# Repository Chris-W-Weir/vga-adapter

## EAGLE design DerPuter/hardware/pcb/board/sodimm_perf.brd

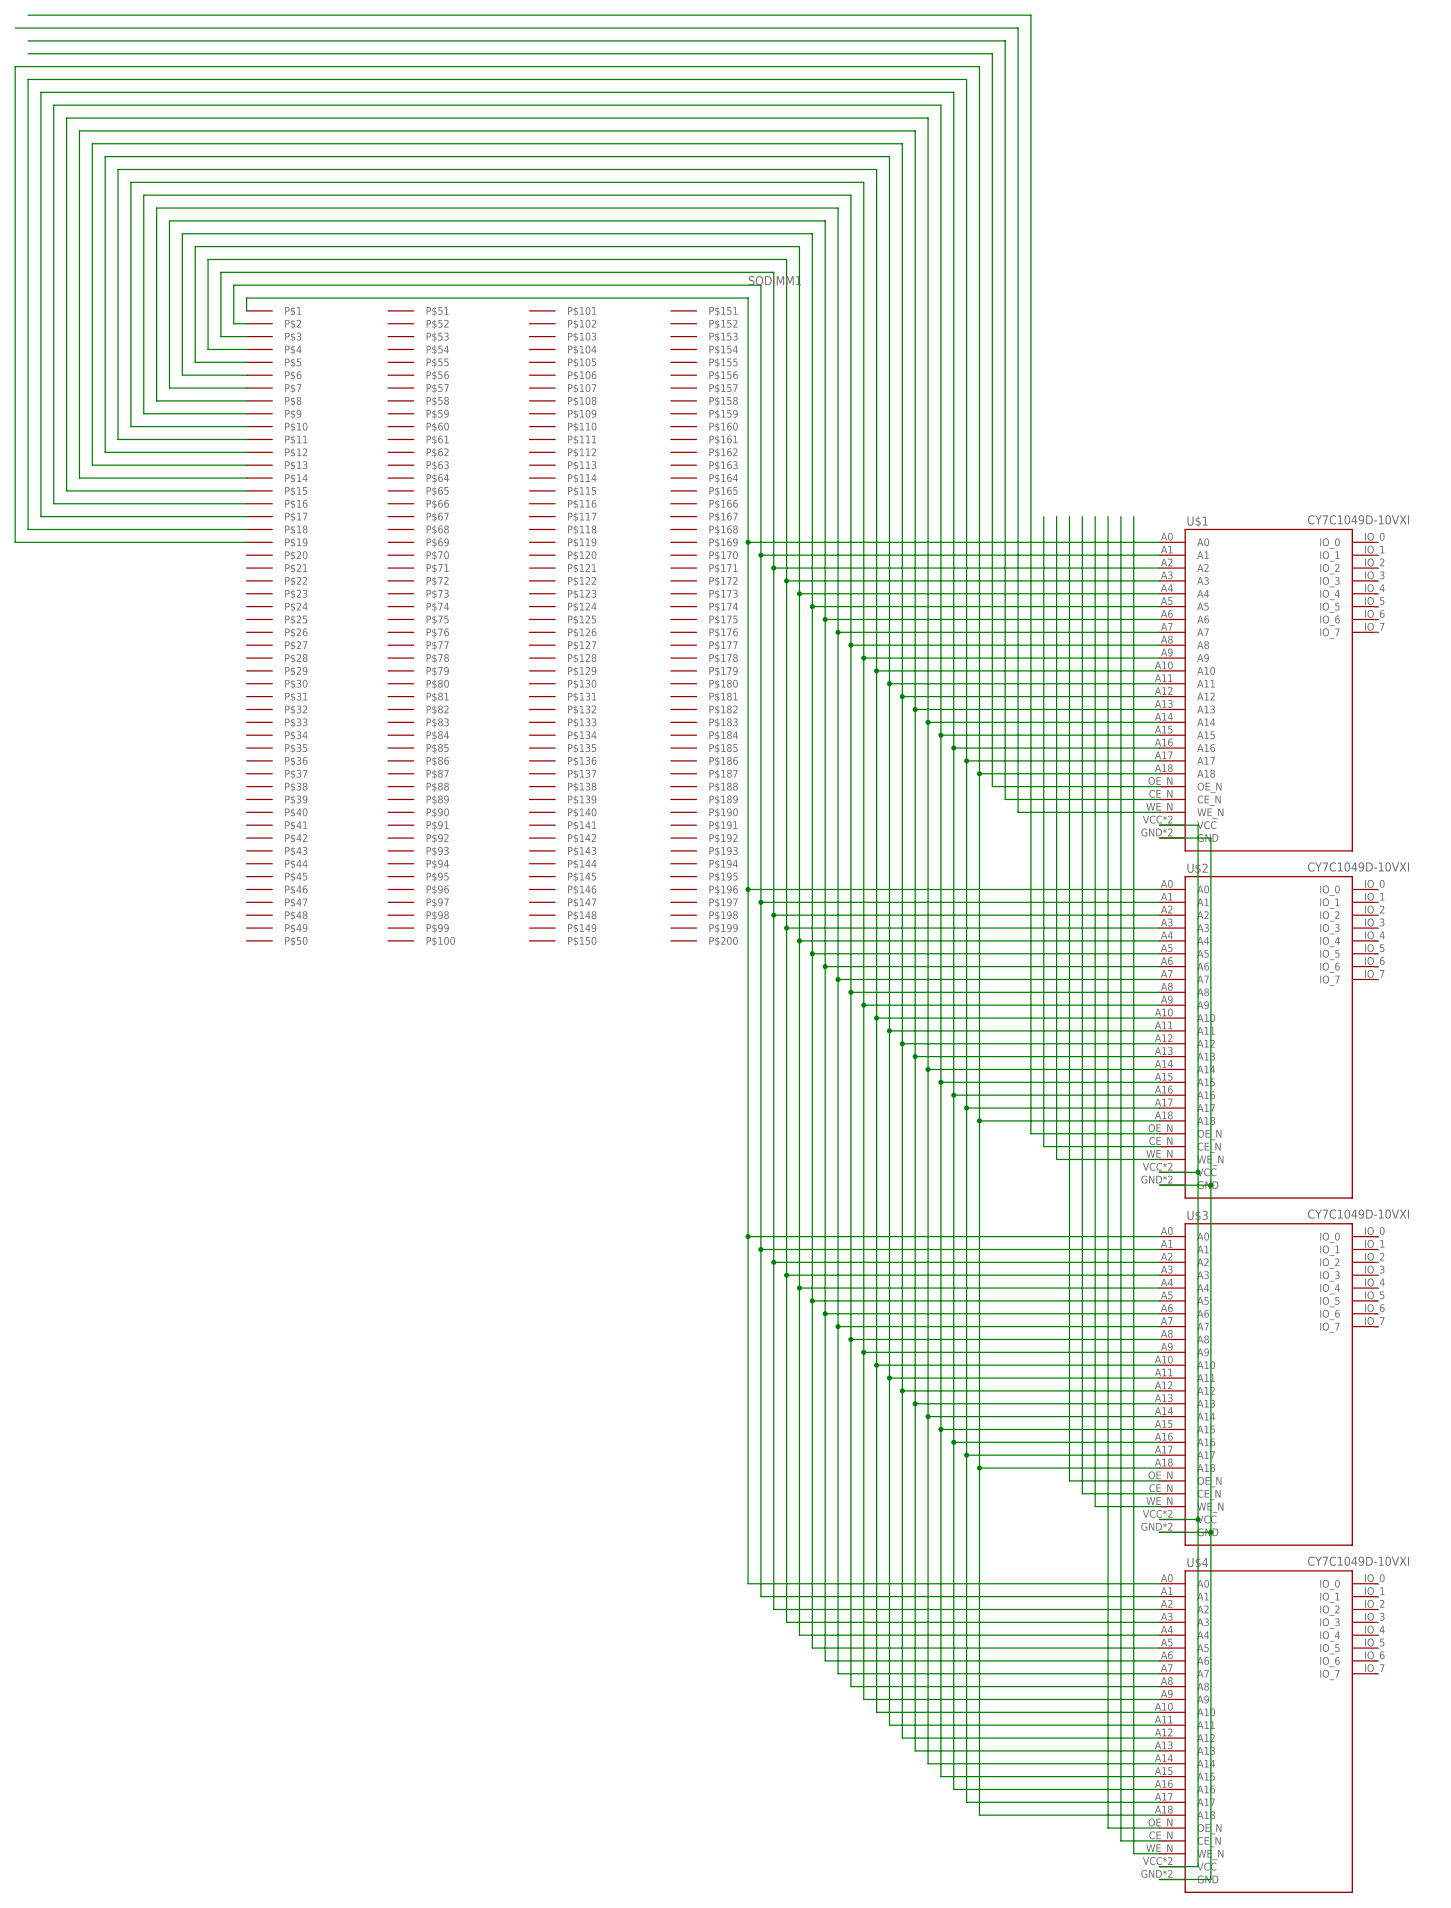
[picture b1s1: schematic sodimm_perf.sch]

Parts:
SODIMM1: SODIMM_BOARD; SODIMM_BOARD-67.6X42.5
U$1, U$2, U$3, U$4: CY7C1049D-10VXI; SOJ36

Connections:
unnamed: SODIMM1.1, U$1.A0, U$2.A0, U$3.A0, U$4.A0
unnamed: SODIMM1.2, U$1.A1, U$2.A1, U$3.A1, U$4.A1
unnamed: SODIMM1.3, U$1.A2, U$2.A2, U$3.A2, U$4.A2
unnamed: SODIMM1.4, U$1.A3, U$2.A3, U$3.A3, U$4.A3
unnamed: SODIMM1.5, U$1.A4, U$2.A4, U$3.A4, U$4.A4
unnamed: SODIMM1.6, U$1.A5, U$2.A5, U$3.A5, U$4.A5
unnamed: SODIMM1.7, U$1.A6, U$2.A6, U$3.A6, U$4.A6
unnamed: SODIMM1.10, U$1.A9, U$2.A9, U$3.A9, U$4.A9
unnamed: SODIMM1.11, U$1.A10, U$2.A10, U$3.A10, U$4.A10
unnamed: SODIMM1.12, U$1.A11, U$2.A11, U$3.A11, U$4.A11
unnamed: SODIMM1.13, U$1.A12, U$2.A12, U$3.A12, U$4.A12
unnamed: SODIMM1.14, U$1.A13, U$2.A13, U$3.A13, U$4.A13
unnamed: SODIMM1.15, U$1.A14, U$2.A14, U$3.A14, U$4.A14
unnamed: SODIMM1.16, U$1.A15, U$2.A15, U$3.A15, U$4.A15
unnamed: SODIMM1.8, U$1.A7, U$2.A7, U$3.A7, U$4.A7
unnamed: SODIMM1.9, U$1.A8, U$2.A8, U$3.A8, U$4.A8
unnamed: SODIMM1.17, U$1.A16, U$2.A16, U$3.A16, U$4.A16
unnamed: SODIMM1.18, U$1.A17, U$2.A17, U$3.A17, U$4.A17
unnamed: SODIMM1.19, U$1.A18, U$2.A18, U$3.A18, U$4.A18
unnamed: U$1.VCC, U$1.VCC_ (VCC), U$2.VCC, U$2.VCC_ (VCC), U$3.VCC, U$3.VCC_ (VCC), U$4.VCC, U$4.VCC_ (VCC)
unnamed: U$1.GND, U$1.GND_ (GND), U$2.GND, U$2.GND_ (GND), U$3.GND, U$3.GND_ (GND), U$4.GND, U$4.GND_ (GND)

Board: 2 copper layers, 5 parts (0 on the bottom side), 21 nets, no tracks yet.

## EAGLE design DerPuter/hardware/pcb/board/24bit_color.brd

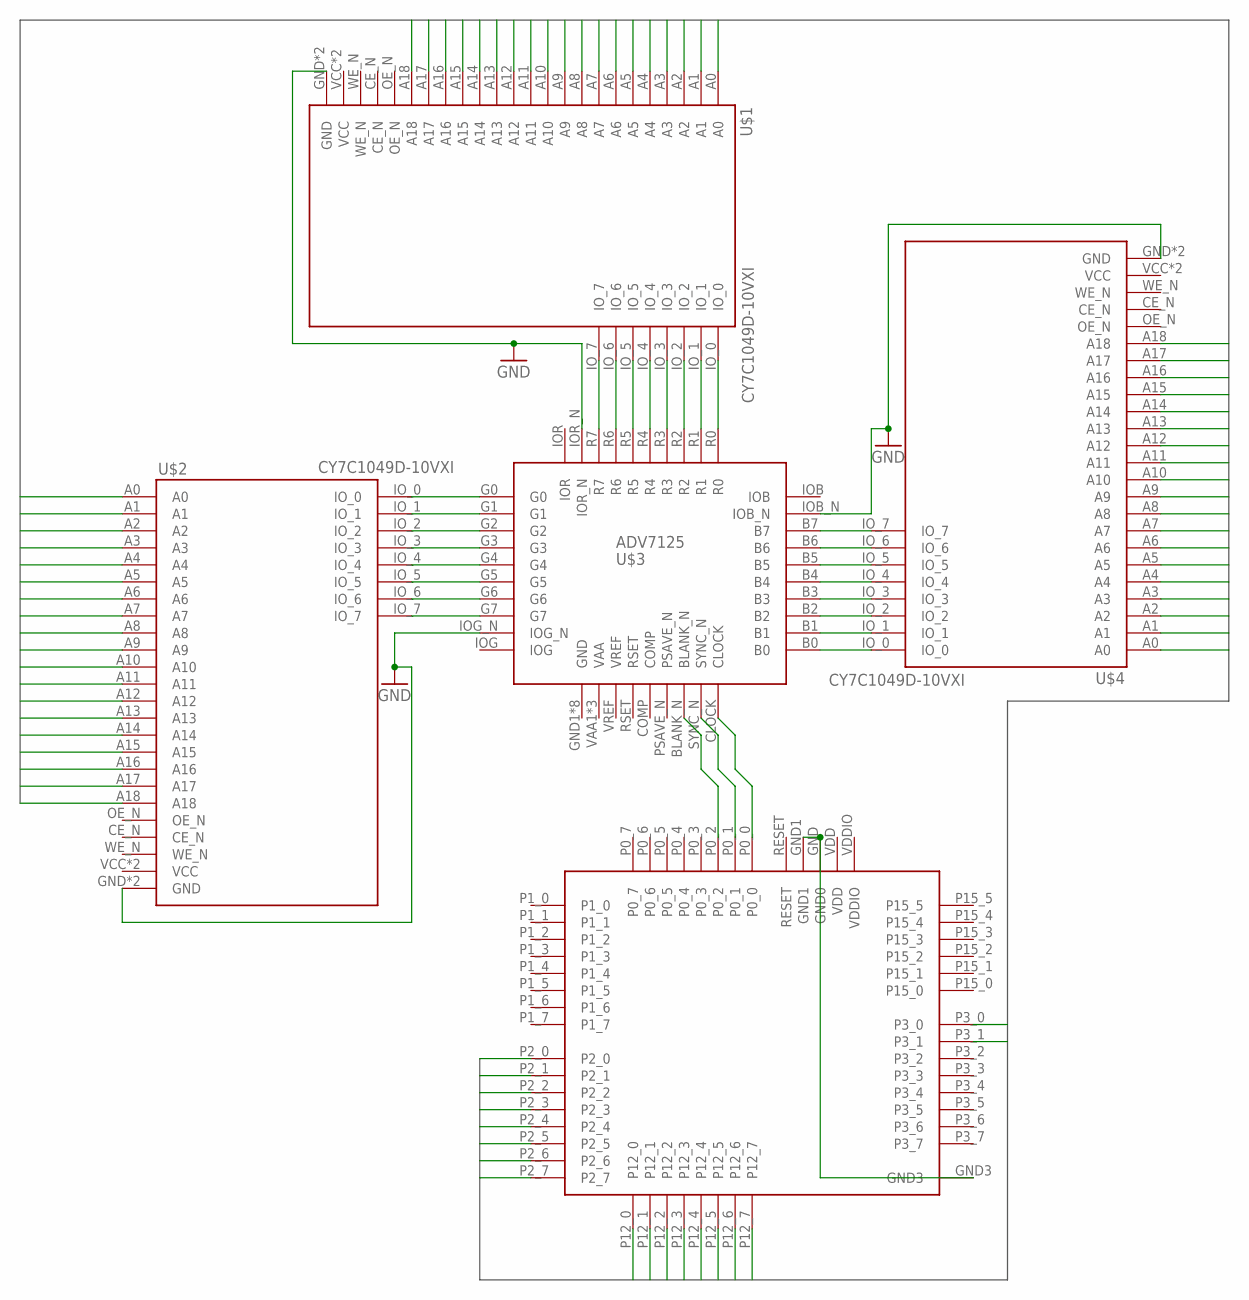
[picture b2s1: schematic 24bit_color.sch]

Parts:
U$1, U$2, U$4: CY7C1049D-10VXI; SOJ36
U$3: ADV7125; LQFP48
U$5: CY8CKIT-059; PSOC_STICK

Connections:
ADR0: U$1.A0, U$2.A0, U$4.A0, U$5.P2_0
ADR1: U$1.A1, U$2.A1, U$4.A1, U$5.P2_1
ADR2: U$1.A2, U$2.A2, U$4.A2, U$5.P2_2
ADR3: U$1.A3, U$2.A3, U$4.A3, U$5.P2_3
ADR4: U$1.A4, U$2.A4, U$4.A4, U$5.P2_4
ADR5: U$1.A5, U$2.A5, U$4.A5, U$5.P2_5
ADR6: U$1.A6, U$2.A6, U$4.A6, U$5.P2_6
ADR7: U$1.A7, U$2.A7, U$4.A7, U$5.P2_7
ADR8: U$1.A8, U$2.A8, U$4.A8, U$5.P12_0
ADR9: U$1.A9, U$2.A9, U$4.A9, U$5.P12_1
ADR10: U$1.A10, U$2.A10, U$4.A10, U$5.P12_2
ADR11: U$1.A11, U$2.A11, U$4.A11, U$5.P12_3
ADR12: U$1.A12, U$2.A12, U$4.A12, U$5.P12_4
ADR13: U$1.A13, U$2.A13, U$4.A13, U$5.P12_5
ADR14: U$1.A14, U$2.A14, U$4.A14, U$5.P12_6
ADR15: U$1.A15, U$2.A15, U$4.A15, U$5.P12_7
ADR16: U$1.A16, U$2.A16, U$4.A16, U$5.P3_0
ADR17: U$1.A17, U$2.A17, U$4.A17, U$5.P3_1
ADR18: U$1.A18, U$2.A18, U$4.A18
GND: U$1.GND, U$1.GND_ (GND), U$2.GND, U$2.GND_ (GND), U$3.GND1 (GND), U$3.GND2 (GND), U$3.GND3 (GND), U$3.GND4 (GND), U$3.GND5 (GND), U$3.GND6 (GND), U$3.GND7 (GND), U$3.GND8 (GND), U$3.IOB_N, U$3.IOG_N, U$3.IOR_N, U$4.GND, U$4.GND_ (GND)
unnamed: U$2.IO_0, U$3.G0
unnamed: U$2.IO_1, U$3.G1
unnamed: U$2.IO_2, U$3.G2
unnamed: U$2.IO_3, U$3.G3
unnamed: U$2.IO_4, U$3.G4
unnamed: U$2.IO_5, U$3.G5
unnamed: U$2.IO_6, U$3.G6
unnamed: U$2.IO_7, U$3.G7
unnamed: U$1.IO_0, U$3.R0
unnamed: U$1.IO_1, U$3.R1
unnamed: U$1.IO_2, U$3.R2
unnamed: U$1.IO_3, U$3.R3
unnamed: U$1.IO_4, U$3.R4
unnamed: U$1.IO_5, U$3.R5
unnamed: U$1.IO_6, U$3.R6
unnamed: U$1.IO_7, U$3.R7
unnamed: U$3.B7, U$4.IO_7
unnamed: U$3.B6, U$4.IO_6
unnamed: U$3.B5, U$4.IO_5
unnamed: U$3.B4, U$4.IO_4
unnamed: U$3.B3, U$4.IO_3
unnamed: U$3.B2, U$4.IO_2
unnamed: U$3.B1, U$4.IO_1
unnamed: U$3.B0, U$4.IO_0
unnamed: U$3.CLOCK, U$5.P0_0
unnamed: U$5.GND (GND0), U$5.GND1, U$5.GND3
unnamed: U$3.SYNC_N, U$5.P0_1
unnamed: U$3.BLANK_N, U$5.P0_2
VAA: U$3.VAA1 (VAA), U$3.VAA2 (VAA), U$3.VAA3 (VAA)
VCC: U$1.VCC, U$1.VCC_ (VCC), U$2.VCC, U$2.VCC_ (VCC), U$4.VCC, U$4.VCC_ (VCC)
VDD: U$5.VDD
VDDIO: U$5.VDDIO

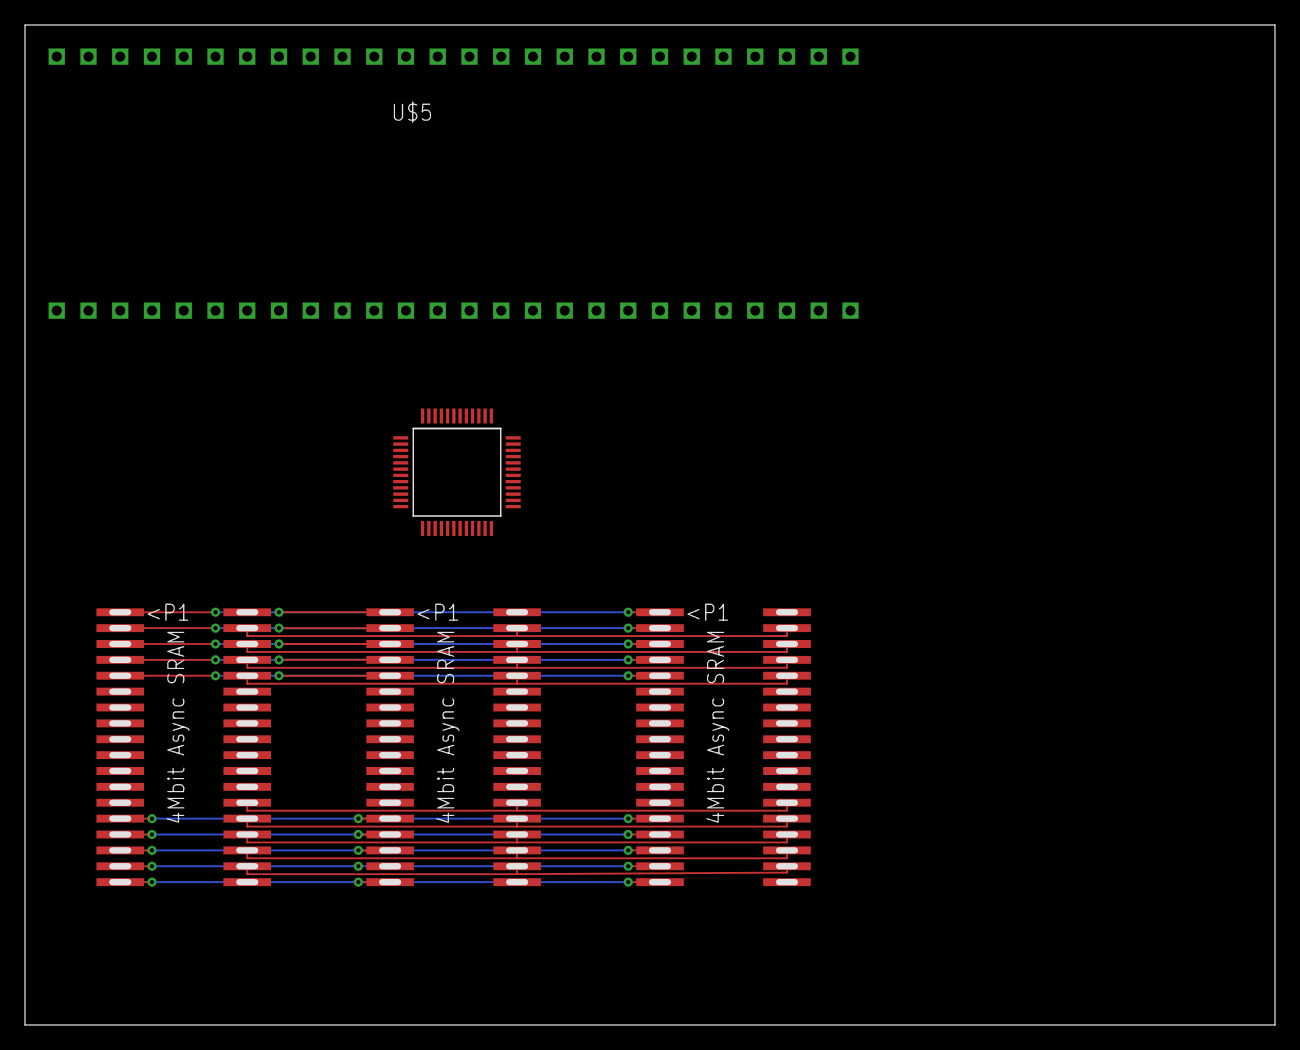
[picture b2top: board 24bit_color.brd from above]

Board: 2 copper layers, 100.0 x 80.0 mm, 5 parts (0 on the bottom side), 50 nets.

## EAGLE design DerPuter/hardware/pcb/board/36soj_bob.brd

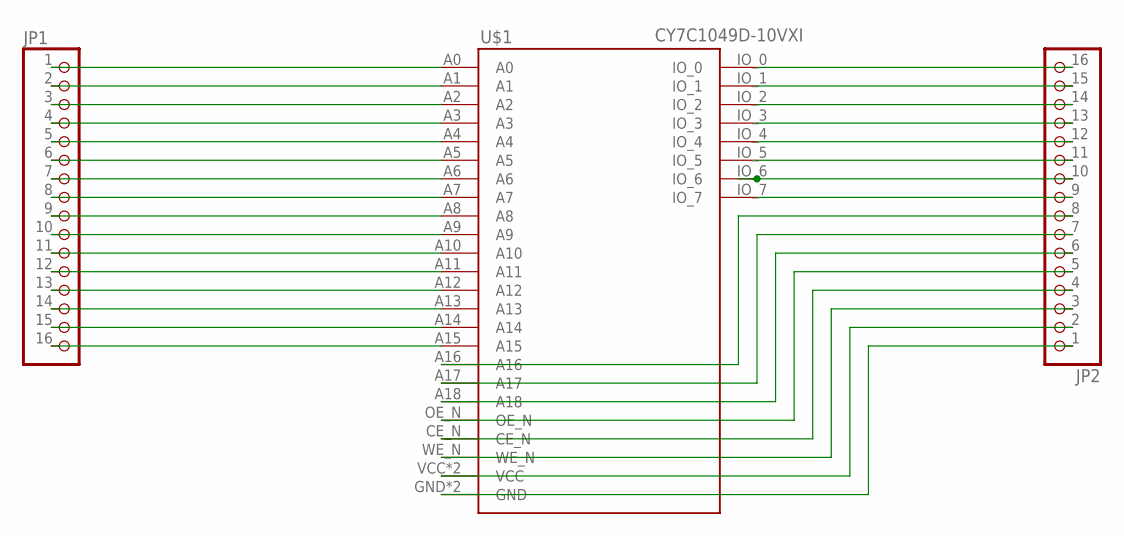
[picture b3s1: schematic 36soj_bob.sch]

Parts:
JP1, JP2: PINHD-1X16; 1X16
U$1: CY7C1049D-10VXI; SOJ36

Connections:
unnamed: JP2.16, U$1.IO_0
unnamed: JP2.15, U$1.IO_1
unnamed: JP2.14, U$1.IO_2
unnamed: JP2.13, U$1.IO_3
unnamed: JP2.12, U$1.IO_4
unnamed: JP2.11, U$1.IO_5
unnamed: JP2.10, U$1.IO_6
unnamed: JP2.9, U$1.IO_7
unnamed: JP1.1, U$1.A0
unnamed: JP1.2, U$1.A1
unnamed: JP1.3, U$1.A2
unnamed: JP1.4, U$1.A3
unnamed: JP1.5, U$1.A4
unnamed: JP1.6, U$1.A5
unnamed: JP1.7, U$1.A6
unnamed: JP1.8, U$1.A7
unnamed: JP1.9, U$1.A8
unnamed: JP1.10, U$1.A9
unnamed: JP1.11, U$1.A10
unnamed: JP1.12, U$1.A11
unnamed: JP1.13, U$1.A12
unnamed: JP1.14, U$1.A13
unnamed: JP1.15, U$1.A14
unnamed: JP1.16, U$1.A15
unnamed: JP2.8, U$1.A16
unnamed: JP2.7, U$1.A17
unnamed: JP2.6, U$1.A18
unnamed: JP2.5, U$1.OE_N
unnamed: JP2.4, U$1.CE_N
unnamed: JP2.3, U$1.WE_N
unnamed: JP2.2, U$1.VCC, U$1.VCC_ (VCC)
unnamed: JP2.1, U$1.GND, U$1.GND_ (GND)

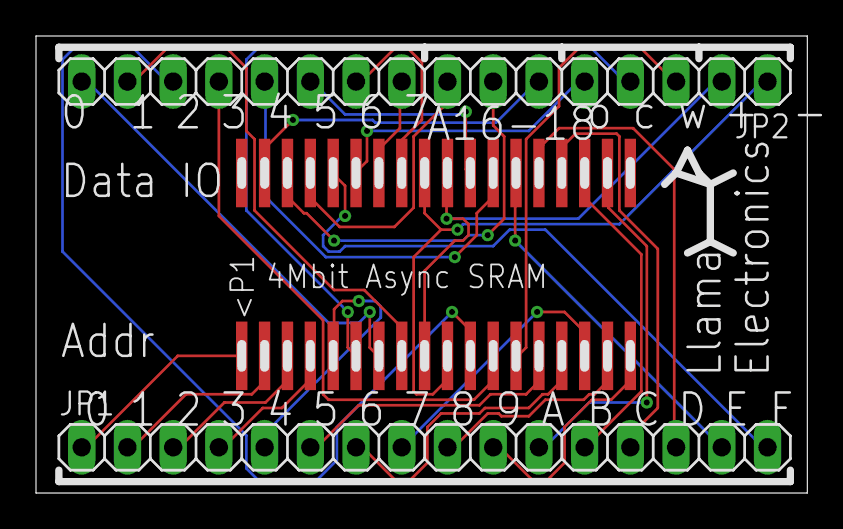
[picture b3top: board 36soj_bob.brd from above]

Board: 2 copper layers, 42.8 x 25.4 mm, 3 parts (0 on the bottom side), 32 nets.

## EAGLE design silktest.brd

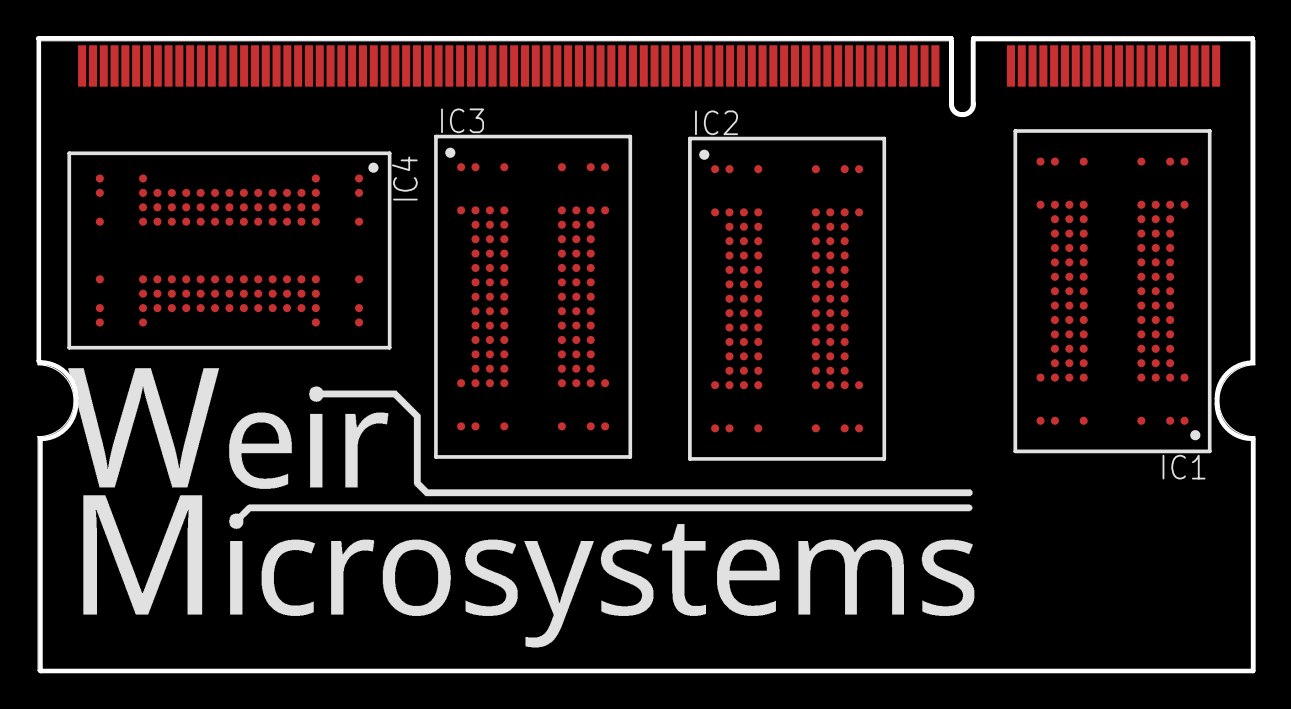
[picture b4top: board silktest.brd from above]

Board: 2 copper layers, 67.5 x 35.1 mm, 5 parts (0 on the bottom side), 86 nets, no tracks yet.

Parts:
IC1, IC2, IC3, IC4: K4B1G04(08/16)46C-128MB; FBGA-94-C
SODIMM1: SODIMM_BOARD_SMALLER-67.6X35

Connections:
unnamed: IC1.K4, SODIMM1.10
unnamed: IC1.J4, SODIMM1.9
unnamed: IC1.N4, SODIMM1.12
unnamed: IC1.P8, SODIMM1.13
unnamed: IC1.P4, SODIMM1.14
unnamed: IC1.N3, SODIMM1.15
unnamed: IC1.P9, SODIMM1.16
unnamed: IC1.P3, SODIMM1.17
unnamed: IC1.R9, SODIMM1.18
unnamed: IC1.R3, SODIMM1.19
unnamed: IC1.T9, SODIMM1.20
unnamed: IC1.R4, SODIMM1.21
unnamed: IC1.L8, SODIMM1.22
unnamed: IC1.R8, SODIMM1.23
unnamed: IC1.N8, SODIMM1.24
unnamed: IC1.H2, SODIMM1.1
unnamed: IC1.L9, SODIMM1.4
unnamed: IC1.M9, SODIMM1.2
unnamed: IC1.T3, SODIMM1.3
unnamed: IC1.L3, SODIMM1.11
unnamed: IC1.E8, SODIMM1.25
unnamed: IC2.K4, SODIMM1.36
unnamed: IC2.J4, SODIMM1.35
unnamed: IC2.N4, SODIMM1.38
unnamed: IC2.P8, SODIMM1.39
unnamed: IC2.P4, SODIMM1.40
unnamed: IC2.N3, SODIMM1.41
unnamed: IC2.P9, SODIMM1.42
unnamed: IC2.P3, SODIMM1.43
unnamed: IC2.R9, SODIMM1.44
unnamed: IC2.R3, SODIMM1.45
unnamed: IC2.T9, SODIMM1.46
unnamed: IC2.R4, SODIMM1.47
unnamed: IC2.L8, SODIMM1.48
unnamed: IC2.R8, SODIMM1.49
unnamed: IC2.N8, SODIMM1.50
unnamed: IC2.H2, SODIMM1.27
unnamed: IC2.L9, SODIMM1.30
unnamed: IC2.M9, SODIMM1.28
unnamed: IC1.L4, SODIMM1.26
unnamed: IC1.G4, SODIMM1.51
unnamed: IC1.F4, SODIMM1.52
unnamed: IC1.M3, SODIMM1.53
unnamed: IC1.N9, SODIMM1.54
unnamed: IC1.M4, SODIMM1.55
unnamed: IC1.E4, SODIMM1.56
unnamed: IC1.F8, SODIMM1.57
unnamed: IC1.F3, SODIMM1.58
unnamed: IC1.F9, SODIMM1.59
unnamed: IC2.T3, SODIMM1.60
unnamed: IC3.K4, SODIMM1.186
unnamed: IC3.J4, SODIMM1.185
unnamed: IC3.N4, SODIMM1.188
unnamed: IC3.P8, SODIMM1.189
unnamed: IC3.P4, SODIMM1.190
unnamed: IC3.N3, SODIMM1.191
unnamed: IC3.P9, SODIMM1.192
unnamed: IC3.P3, SODIMM1.193
unnamed: IC3.R9, SODIMM1.194
unnamed: IC3.R3, SODIMM1.195
unnamed: IC3.T9, SODIMM1.196
unnamed: IC3.R4, SODIMM1.197
unnamed: IC3.L8, SODIMM1.198
unnamed: IC3.R8, SODIMM1.199
unnamed: IC3.N8, SODIMM1.200
unnamed: IC3.H2, SODIMM1.177
unnamed: IC3.L9, SODIMM1.180
unnamed: IC3.M9, SODIMM1.178
unnamed: IC4.K4, SODIMM1.160
unnamed: IC4.J4, SODIMM1.159
unnamed: IC4.N4, SODIMM1.162
unnamed: IC4.P8, SODIMM1.163
unnamed: IC4.P4, SODIMM1.164
unnamed: IC4.N3, SODIMM1.165
unnamed: IC4.P9, SODIMM1.166
unnamed: IC4.P3, SODIMM1.167
unnamed: IC4.R9, SODIMM1.168
unnamed: IC4.R3, SODIMM1.169
unnamed: IC4.T9, SODIMM1.170
unnamed: IC4.R4, SODIMM1.171
unnamed: IC4.L8, SODIMM1.172
unnamed: IC4.R8, SODIMM1.173
unnamed: IC4.N8, SODIMM1.174
unnamed: IC4.H2, SODIMM1.151
unnamed: IC4.L9, SODIMM1.154
unnamed: IC4.M9, SODIMM1.152

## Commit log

2015-12-02 :octocat: Added .gitattributes
2015-12-02 Adding initial progress
    Not all of this is particularly useful, will clean up later
2016-03-24 New directory structure such that it actually makes any sense
2016-03-24 files moved, I'm bad at git
2016-03-24 starting work on the stupid rom generator script to create framebuffer tests
